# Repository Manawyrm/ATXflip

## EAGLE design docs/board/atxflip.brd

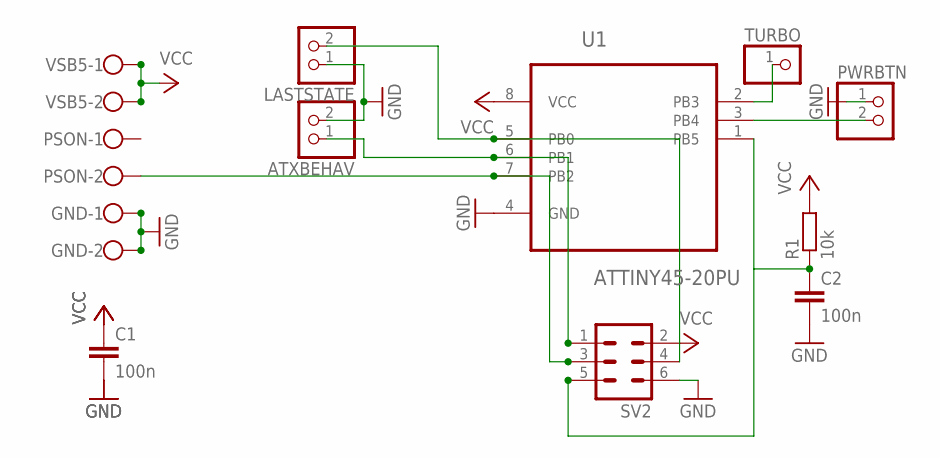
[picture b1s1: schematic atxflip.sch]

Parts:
ATXBEHAV: PINHD-1X2; 1X02
C1, C2: 100n; C7.5B3
GND: W237-102
LASTSTATE: PINHD-1X2; 1X02
PSON: W237-102
PWRBTN: PINHD-1X2; 1X02
R1: 10k; 0207/10
SV2: ML6
TURBO: PINHD-1X1; 1X01
U1: ATTINY45-20PU; DIP254P762X533-8
VSB5: W237-102

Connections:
GND: ATXBEHAV.2, C1.2, C2.2, GND.1, GND.2, LASTSTATE.1, PWRBTN.1, SV2.6, U1.4 (GND)
unnamed: PWRBTN.2, U1.3 (PB4)
unnamed: PSON.2, SV2.3, U1.7 (PB2)
unnamed: ATXBEHAV.1, SV2.1, U1.6 (PB1)
unnamed: LASTSTATE.2, SV2.4, U1.5 (PB0)
unnamed: TURBO.1, U1.2 (PB3)
unnamed: C2.1, R1.1, SV2.5, U1.1 (PB5)
VCC: C1.1, R1.2, SV2.2, U1.8 (VCC), VSB5.1, VSB5.2

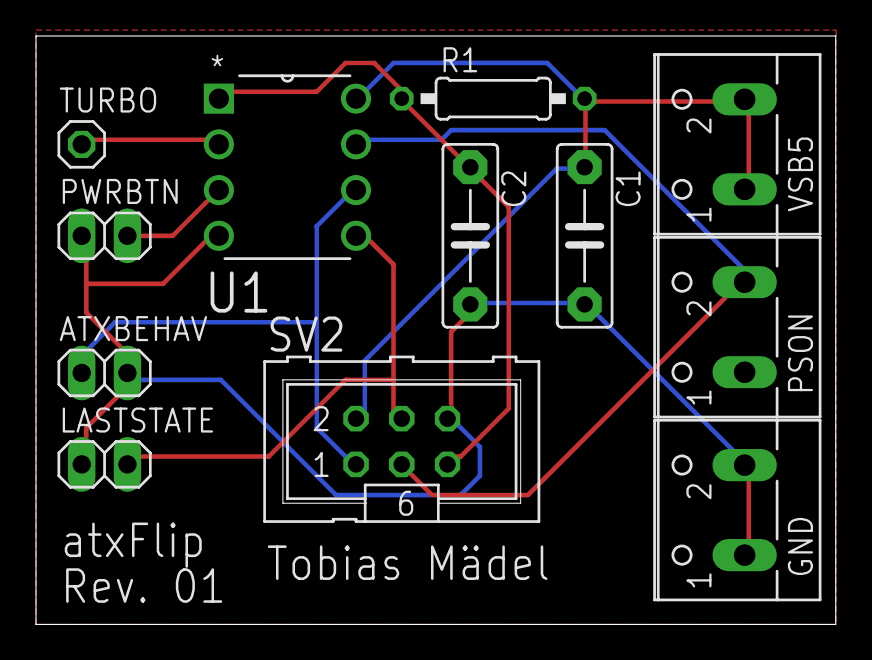
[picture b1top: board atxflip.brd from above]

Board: 2 copper layers, 44.4 x 32.7 mm, 12 parts (0 on the bottom side), 8 nets.

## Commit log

2015-09-13 added pictures
2015-09-13 added schematic and board
2015-10-08 new boards :)
2015-10-08 removed fail *lol*
